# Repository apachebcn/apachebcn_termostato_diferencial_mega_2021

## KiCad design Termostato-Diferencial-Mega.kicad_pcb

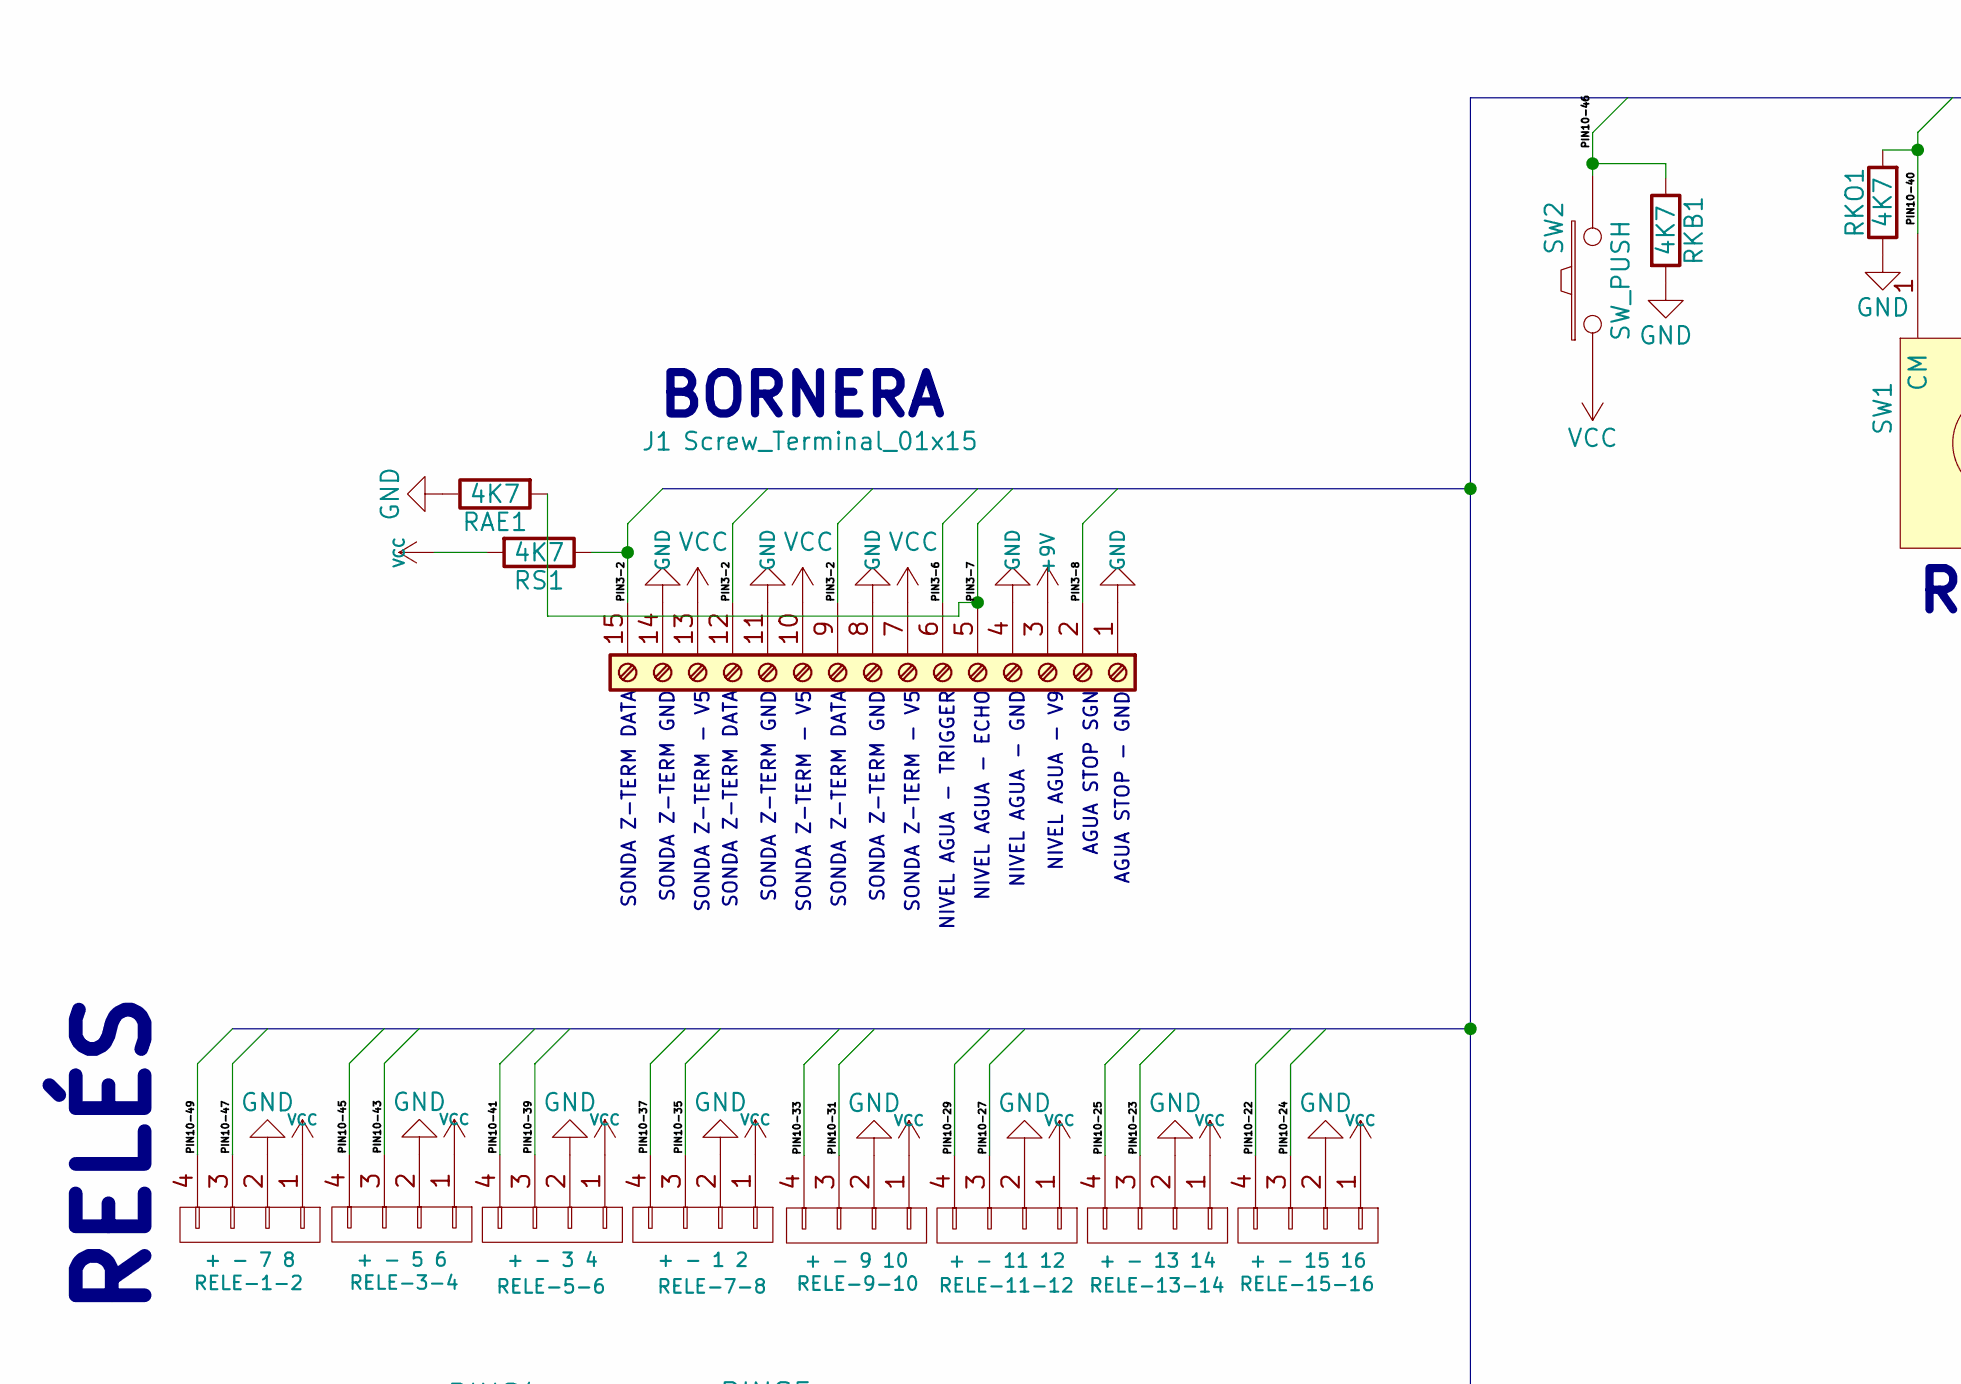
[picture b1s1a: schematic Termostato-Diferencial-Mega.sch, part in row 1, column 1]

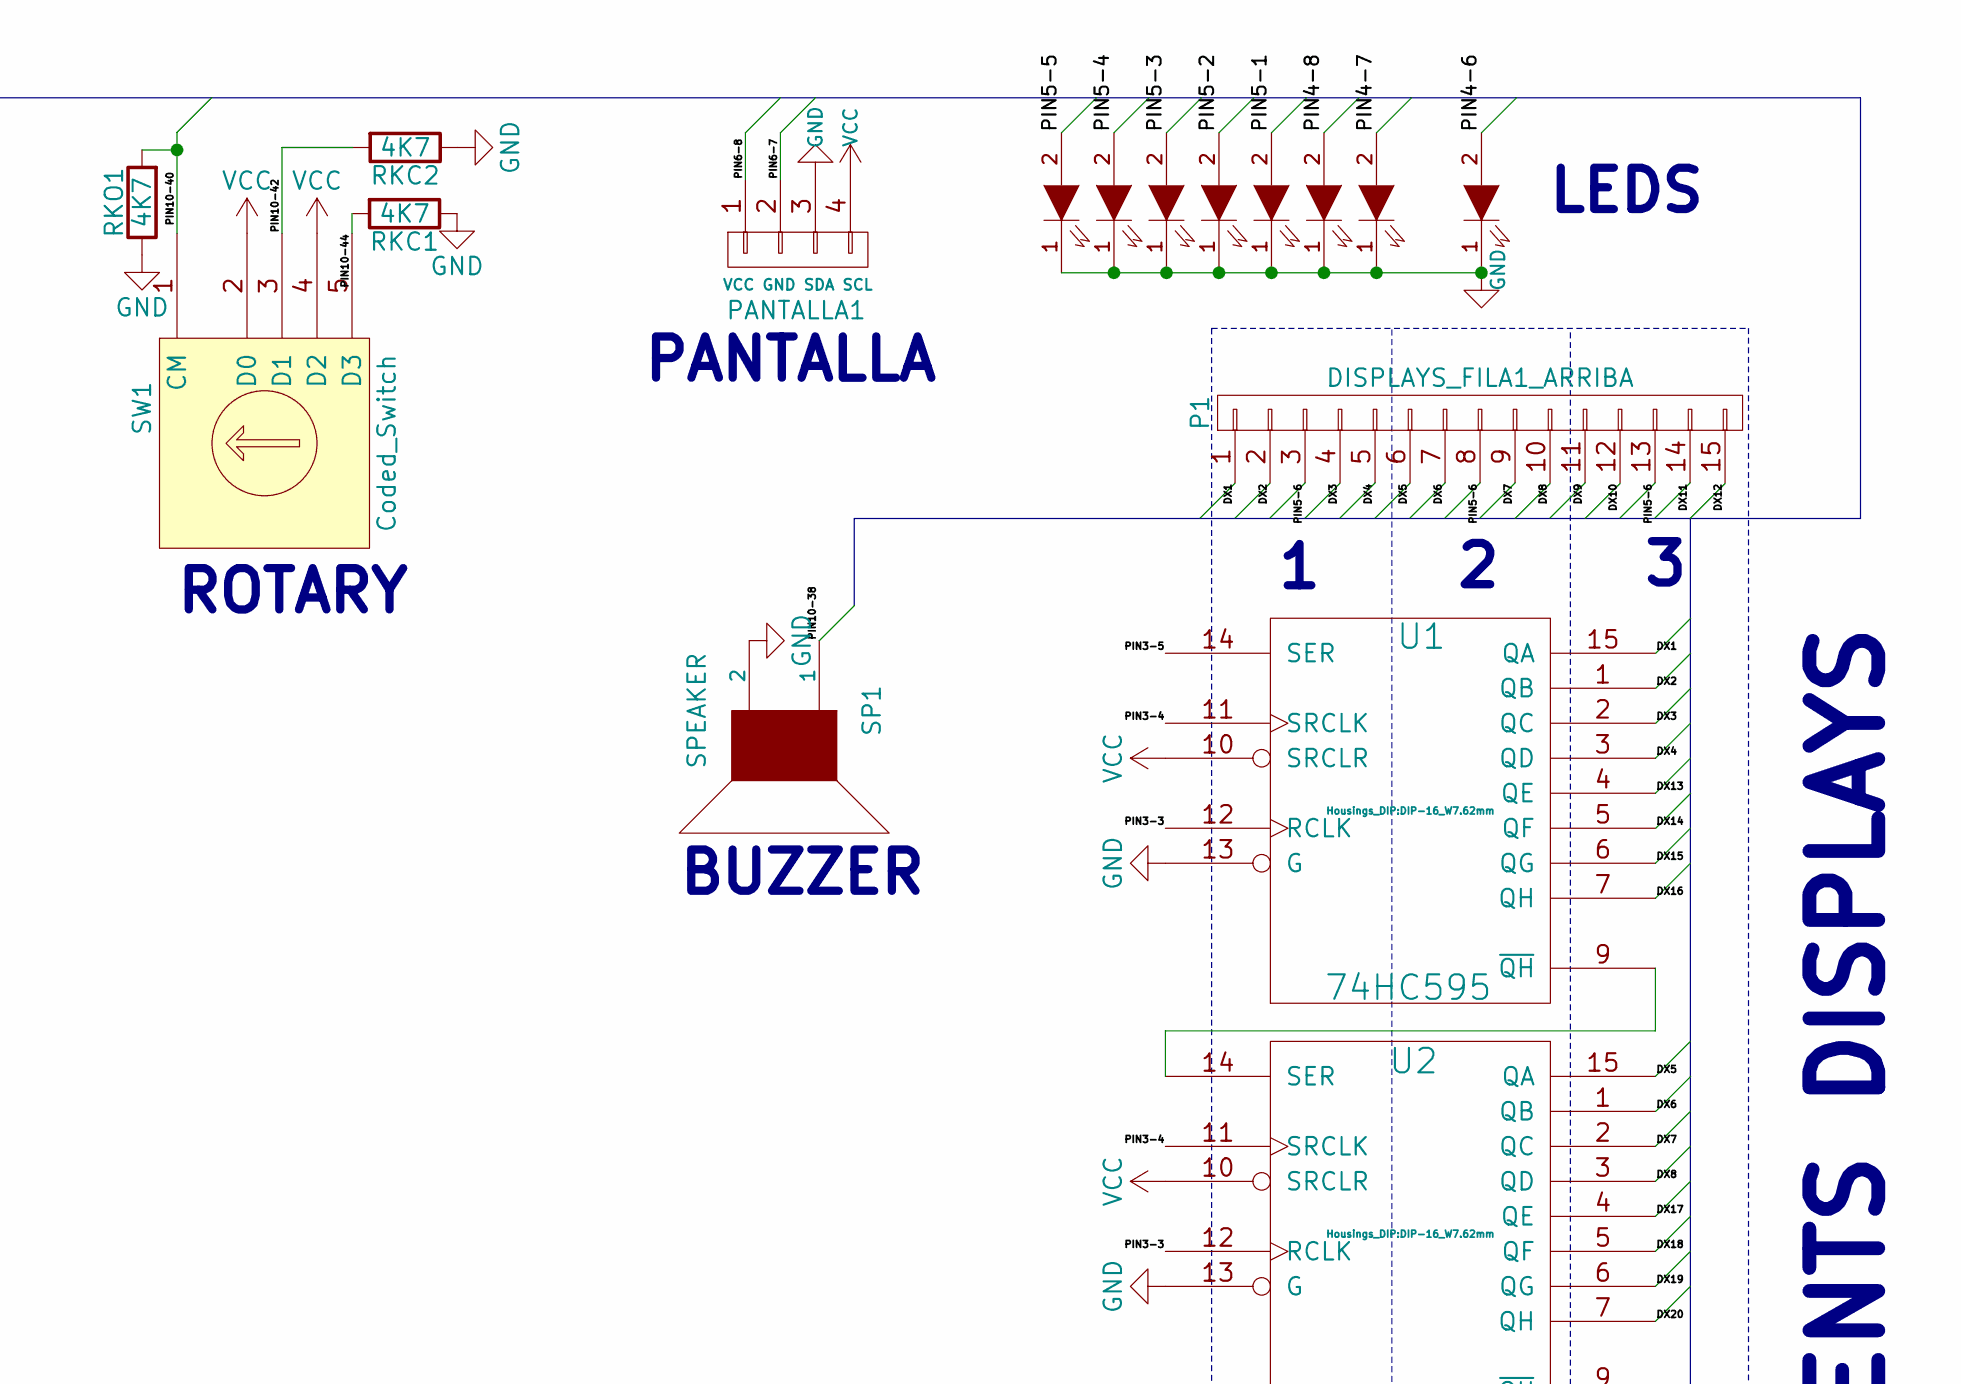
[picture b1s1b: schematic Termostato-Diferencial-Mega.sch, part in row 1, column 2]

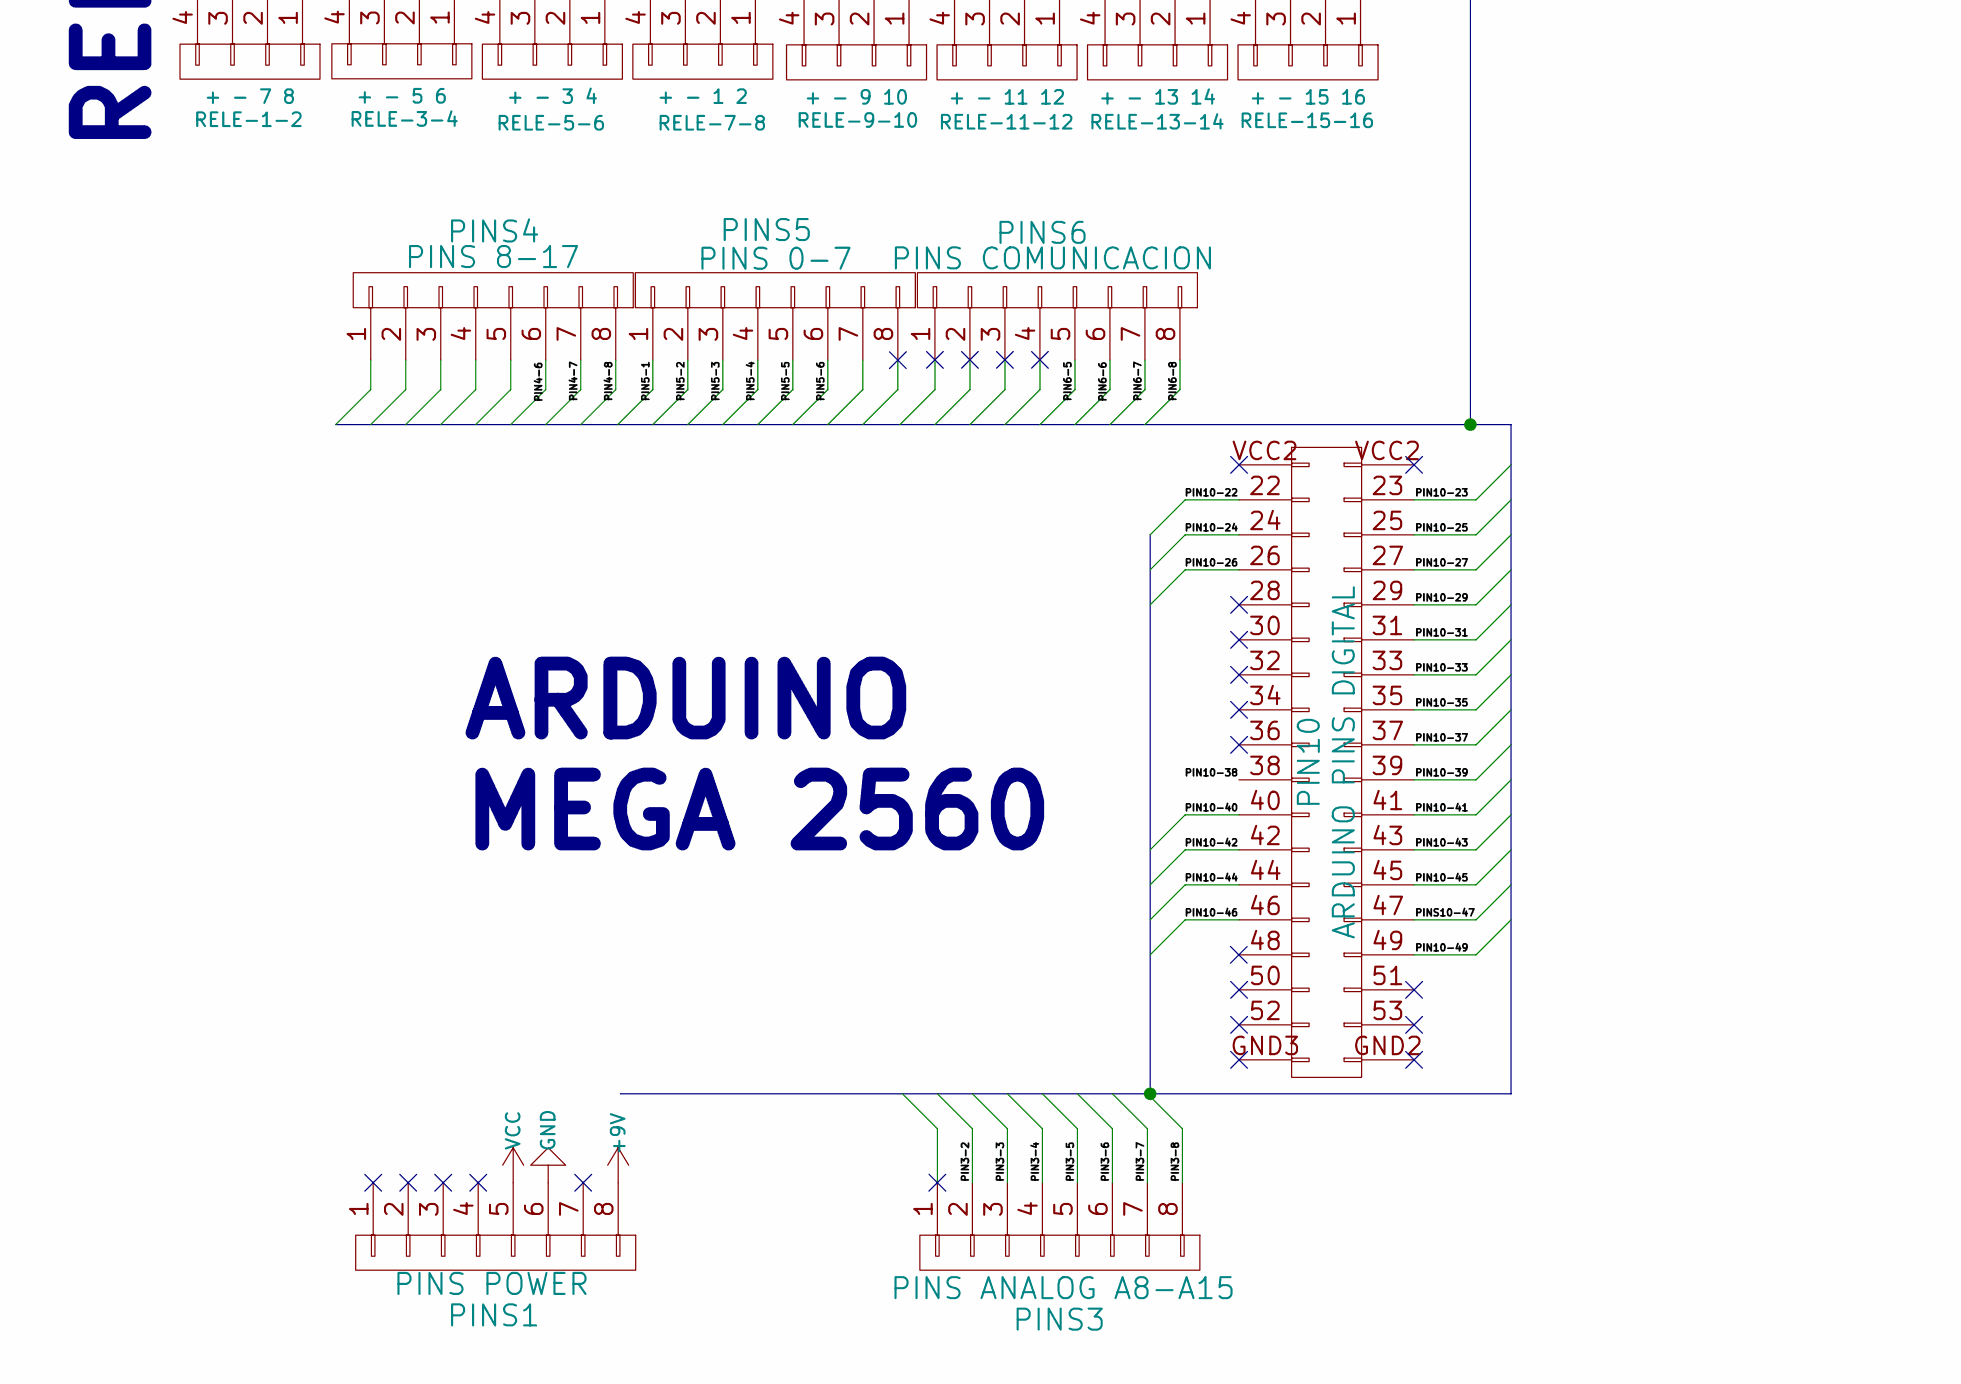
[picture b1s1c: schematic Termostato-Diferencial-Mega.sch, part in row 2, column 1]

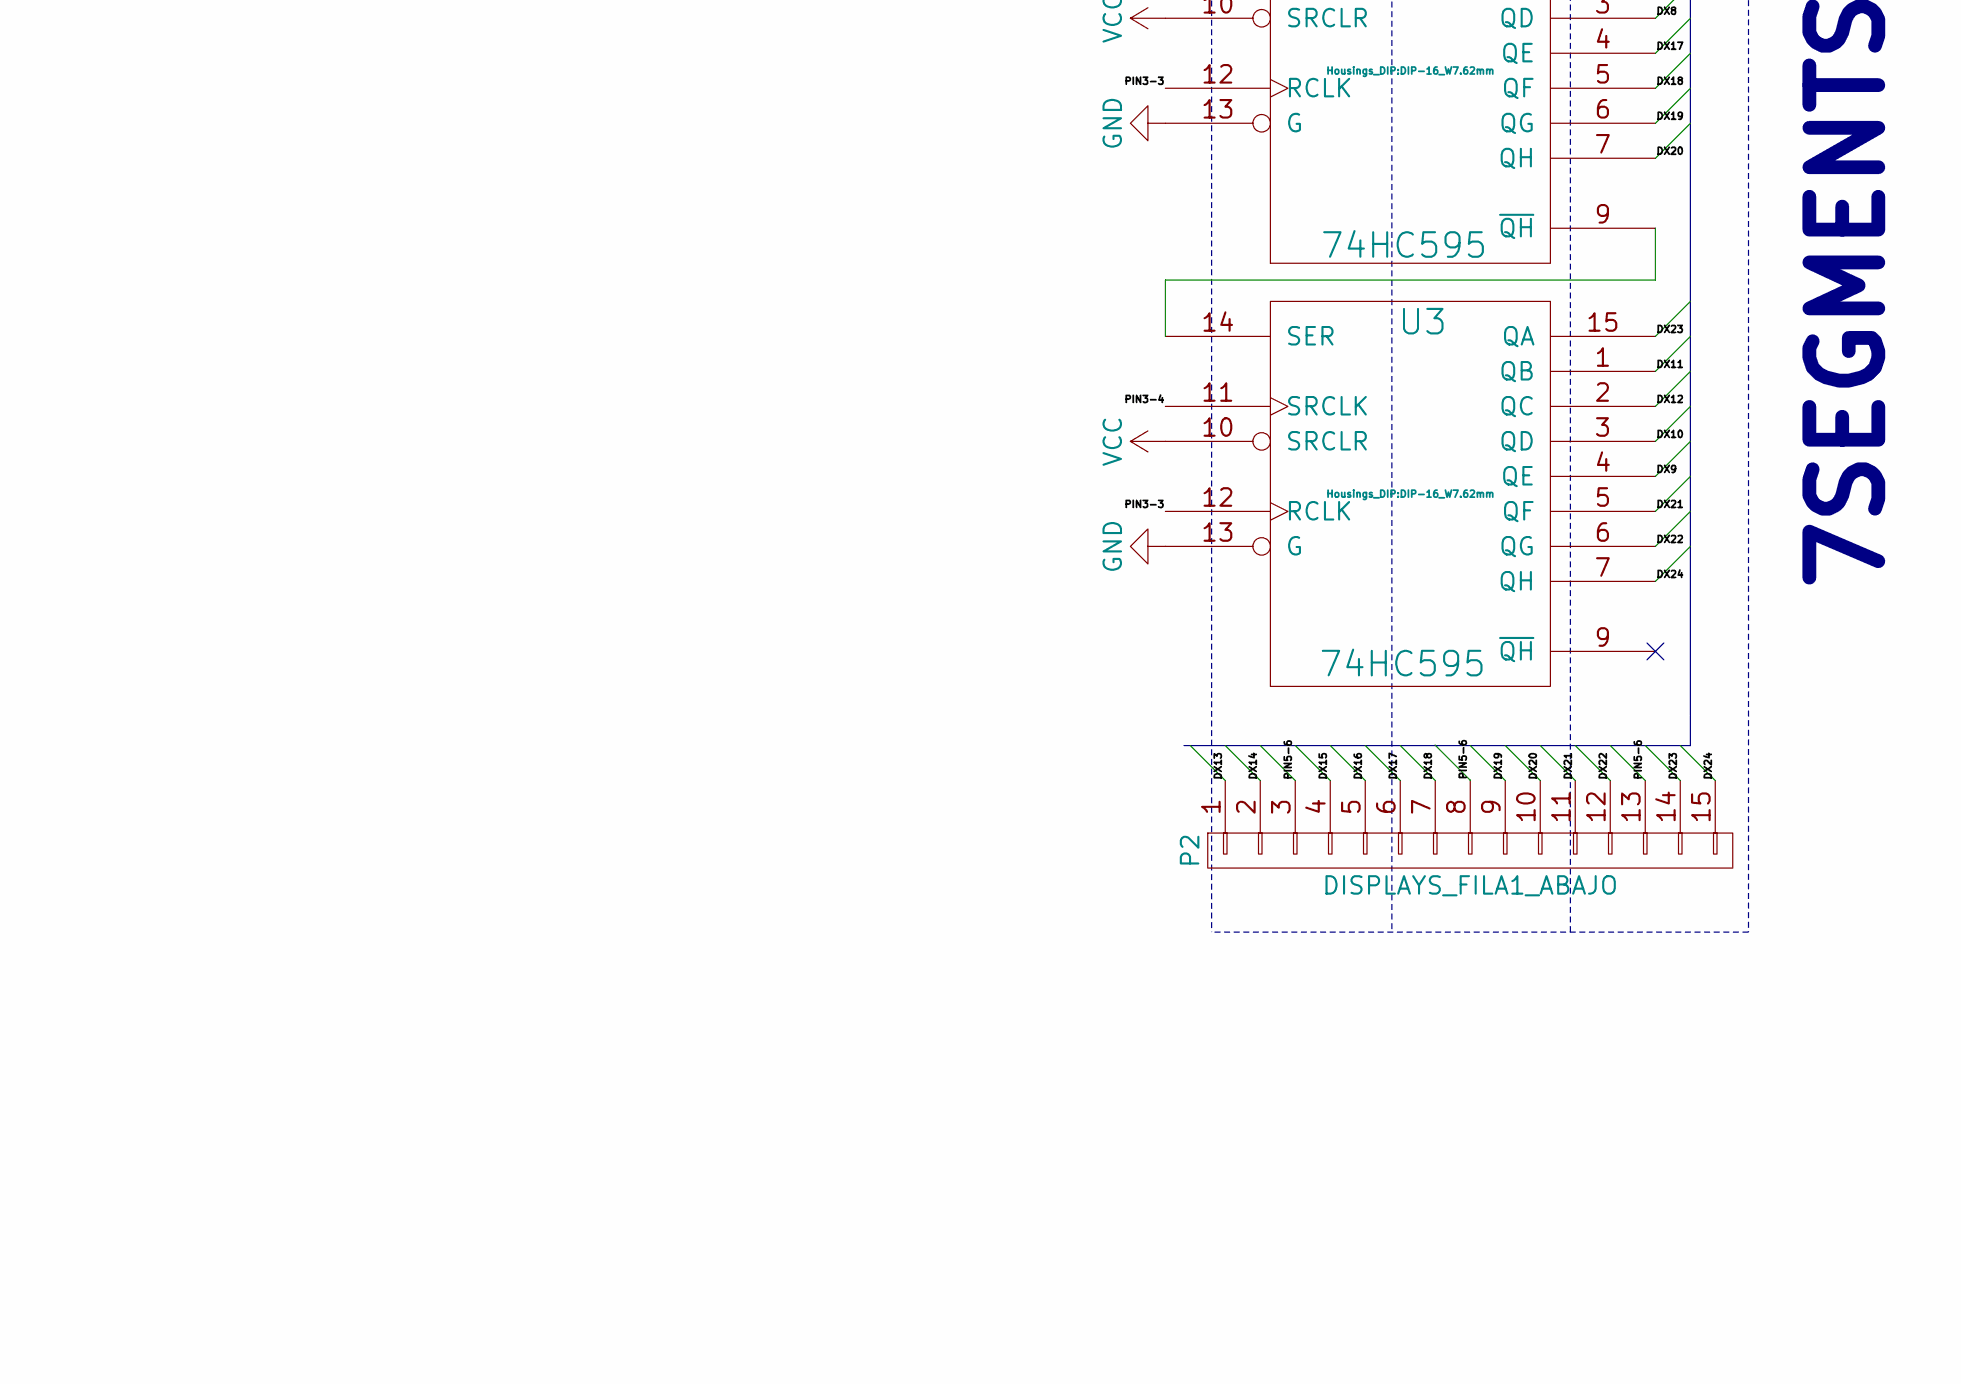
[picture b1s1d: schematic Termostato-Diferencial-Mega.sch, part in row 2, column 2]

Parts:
D1, D2, D3, D4, D5, D6, D7, D8: LED; LED_1206_3216Metric
J1: Screw_Terminal_01x15; TerminalBlock_Phoenix_MKDS-3-15-5.08_1x15_P5.08mm_Horizontal
P1: DISPLAYS_FILA1_ARRIBA; Socket_Strip_Straight_1x15
P2: DISPLAYS_FILA1_ABAJO; Socket_Strip_Straight_1x15
PANTALLA1: VCC GND SDA SCL; PinHeader_1x04_P2.54mm_Vertical
PIN10: ARDUINO PINS DIGITAL; PinHeader_2x18_P2.54mm_Vertical
PINS1: PINS POWER; PinHeader_1x08_P2.54mm_Vertical
PINS3: PINS ANALOG A8-A15; PinHeader_1x08_P2.54mm_Vertical
PINS4: PINS 8-17; PinHeader_1x08_P2.54mm_Vertical
PINS5: PINS 0-7; PinHeader_1x08_P2.54mm_Vertical
PINS6: PINS COMUNICACION; PinHeader_1x08_P2.54mm_Vertical
RAE1: 4K7; R_1206_3216Metric
RELE-1-2: + - 7 8; PinHeader_1x04_P2.54mm_Vertical
RELE-3-4: + - 5 6; PinHeader_1x04_P2.54mm_Vertical
RELE-5-6: + - 3 4; PinHeader_1x04_P2.54mm_Vertical
RELE-7-8: + - 1 2; PinHeader_1x04_P2.54mm_Vertical
RELE-9-10: + - 9 10; PinHeader_1x04_P2.54mm_Vertical
RELE-11-12: + - 11 12; PinHeader_1x04_P2.54mm_Vertical
RELE-13-14: + - 13 14; PinHeader_1x04_P2.54mm_Vertical
RELE-15-16: + - 15 16; PinHeader_1x04_P2.54mm_Vertical
RKB1: 4K7; R_1206_3216Metric
RKC1, RKC2: 4K7; R_1206_3216Metric
RKO1: 4K7; R_1206_3216Metric
RS1: 4K7; R_1206_3216Metric
SP1: SPEAKER; Buzzer_12x9.5RM7.6
SW1: Coded_Switch; KSA_Tactile_SPST
SW2: SW_PUSH; SW_PUSH-12mm
U1, U2, U3: 74HC595; DIP-16_W7.62mm

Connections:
+9V: J1.3, PINS1.8
/DX1: P1.1, U1.15 (QA)
/DX2: P1.2, U1.1 (QB)
/DX3: P1.4, U1.2 (QC)
/DX4: P1.5, U1.3 (QD)
/DX5: P1.6, U2.15 (QA)
/DX6: P1.7, U2.1 (QB)
/DX7: P1.9, U2.2 (QC)
/DX8: P1.10, U2.3 (QD)
/DX9: P1.11, U3.4 (QE)
/DX10: P1.12, U3.3 (QD)
/DX11: P1.14, U3.1 (QB)
/DX12: P1.15, U3.2 (QC)
/DX13: P2.1, U1.4 (QE)
/DX14: P2.2, U1.5 (QF)
/DX15: P2.4, U1.6 (QG)
/DX16: P2.5, U1.7 (QH)
/DX17: P2.6, U2.4 (QE)
/DX18: P2.7, U2.5 (QF)
/DX19: P2.9, U2.6 (QG)
/DX20: P2.10, U2.7 (QH)
/DX21: P2.11, U3.5 (QF)
/DX22: P2.12, U3.6 (QG)
/DX23: P2.14, U3.15 (QA)
/DX24: P2.15, U3.7 (QH)
/PIN3-2: J1.9, J1.12, J1.15, PINS3.2, RS1.1
/PIN3-3: PINS3.3, U1.12 (RCLK), U2.12 (RCLK), U3.12 (RCLK)
/PIN3-4: PINS3.4, U1.11 (SRCLK), U2.11 (SRCLK), U3.11 (SRCLK)
/PIN3-5: PINS3.5, U1.14 (SER)
/PIN3-6: J1.6, PINS3.6
/PIN3-7: J1.5, PINS3.7, RAE1.2
/PIN3-8: J1.2, PINS3.8
/PIN4-6: D1.2 (A), PINS4.6
/PIN4-7: D2.2 (A), PINS4.7
/PIN4-8: D3.2 (A), PINS4.8
/PIN5-1: D4.2 (A), PINS5.1
/PIN5-2: D5.2 (A), PINS5.2
/PIN5-3: D6.2 (A), PINS5.3
/PIN5-4: D7.2 (A), PINS5.4
/PIN5-5: D8.2 (A), PINS5.5
/PIN5-6: P1.3, P1.8, P1.13, P2.3, P2.8, P2.13, PINS5.6
/PIN6-7: PANTALLA1.2, PINS6.7
/PIN6-8: PANTALLA1.1, PINS6.8
/PIN10-22: PIN10.22, RELE-15-16.4
/PIN10-23: PIN10.23, RELE-13-14.3
/PIN10-24: PIN10.24, RELE-15-16.3
/PIN10-25: PIN10.25, RELE-13-14.4
/PIN10-26: PIN10.26
/PIN10-27: PIN10.27, RELE-11-12.3
/PIN10-29: PIN10.29, RELE-11-12.4
/PIN10-31: PIN10.31, RELE-9-10.3
/PIN10-33: PIN10.33, RELE-9-10.4
/PIN10-35: PIN10.35, RELE-7-8.3
/PIN10-37: PIN10.37, RELE-7-8.4
/PIN10-38: PIN10.38, SP1.1
/PIN10-39: PIN10.39, RELE-5-6.3
/PIN10-40: PIN10.40, RKO1.2, SW1.1 (CM)
/PIN10-41: PIN10.41, RELE-5-6.4
/PIN10-42: PIN10.42, RKC2.2, SW1.3 (D1)
/PIN10-43: PIN10.43, RELE-3-4.3
/PIN10-44: PIN10.44, RKC1.2, SW1.5 (D3)
/PIN10-45: PIN10.45, RELE-3-4.4
/PIN10-46: PIN10.46, RKB1.1, SW2.2
/PIN10-49: PIN10.49, RELE-1-2.4
GND: D1.1 (K), D2.1 (K), D3.1 (K), D4.1 (K), D5.1 (K), D6.1 (K), D7.1 (K), D8.1 (K), J1.1, J1.4, J1.8, J1.11, J1.14, PANTALLA1.3, PINS1.6, RAE1.1, RELE-1-2.2, RELE-3-4.2, RELE-5-6.2, RELE-7-8.2, RELE-9-10.2, RELE-11-12.2, RELE-13-14.2, RELE-15-16.2, RKB1.2, RKC1.1, RKC2.1, RKO1.1, SP1.2, U1.8 (GND), U1.13 (G), U2.8 (GND), U2.13 (G), U3.8 (GND), U3.13 (G)
unnamed: U1.9 (~QH), U2.14 (SER)
unnamed: U2.9 (~QH), U3.14 (SER)
VCC: J1.7, J1.10, J1.13, PANTALLA1.4, PINS1.5, RELE-1-2.1, RELE-3-4.1, RELE-5-6.1, RELE-7-8.1, RELE-9-10.1, RELE-11-12.1, RELE-13-14.1, RELE-15-16.1, RS1.2, SW1.2 (D0), SW1.4 (D2), SW2.1, U1.10 (SRCLR), U1.16 (VCC), U2.10 (SRCLR), U2.16 (VCC), U3.10 (SRCLR), U3.16 (VCC)

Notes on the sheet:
AGUA STOP SGN
NIVEL AGUA - V9
NIVEL AGUA - GND
AGUA STOP - GND
NIVEL AGUA - ECHO
SONDA Z-TERM - V5
SONDA Z-TERM GND
SONDA Z-TERM DATA
NIVEL AGUA - TRIGGER
ARDUINO MEGA 2560
RELÉS
7SEGMENTS DISPLAYS
PANTALLA
LEDS
ROTARY
BORNERA
BUZZER

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
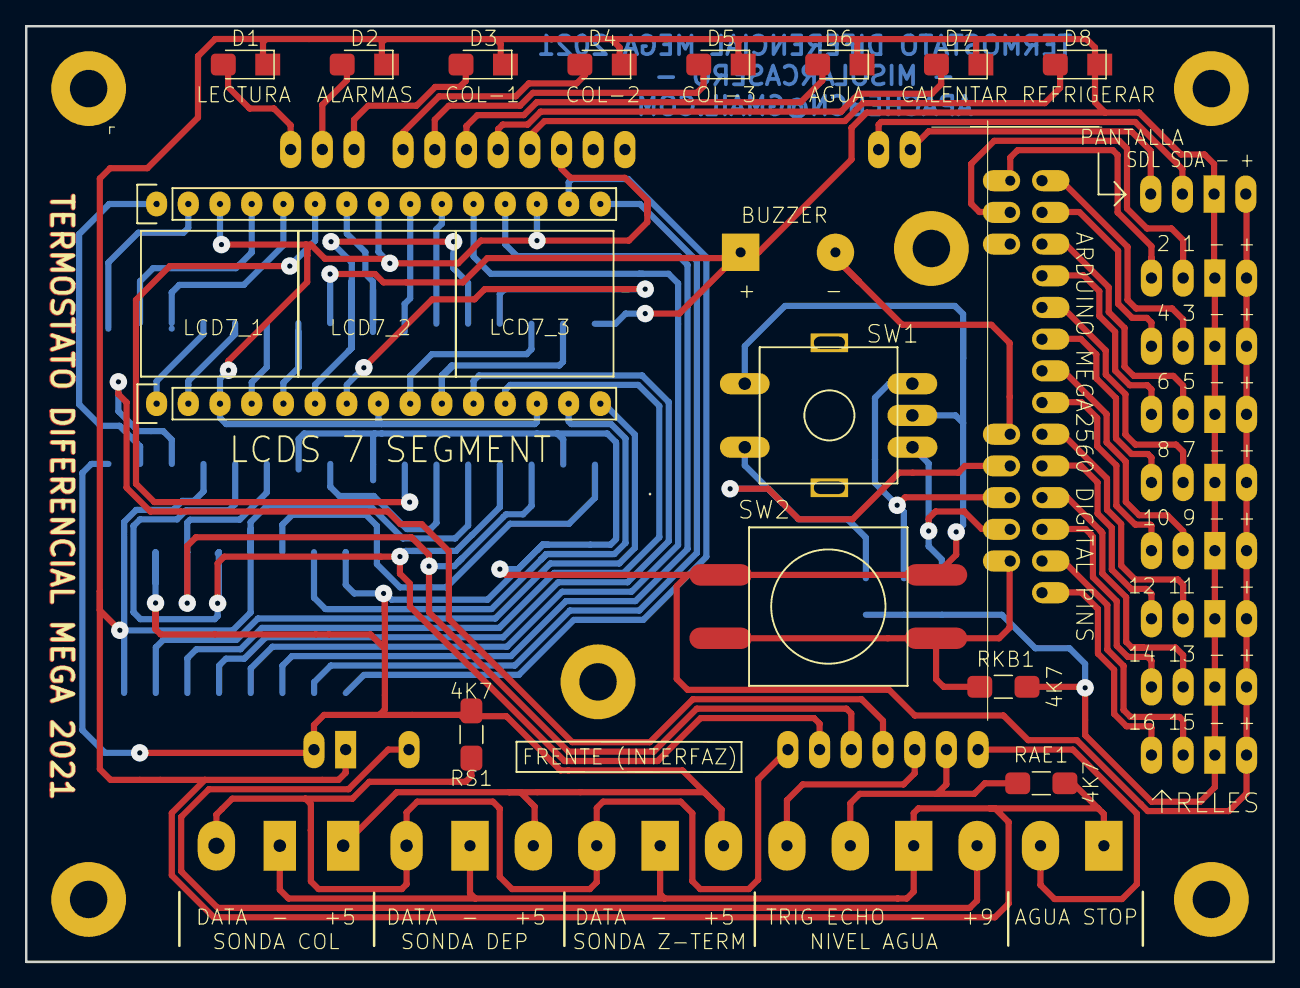
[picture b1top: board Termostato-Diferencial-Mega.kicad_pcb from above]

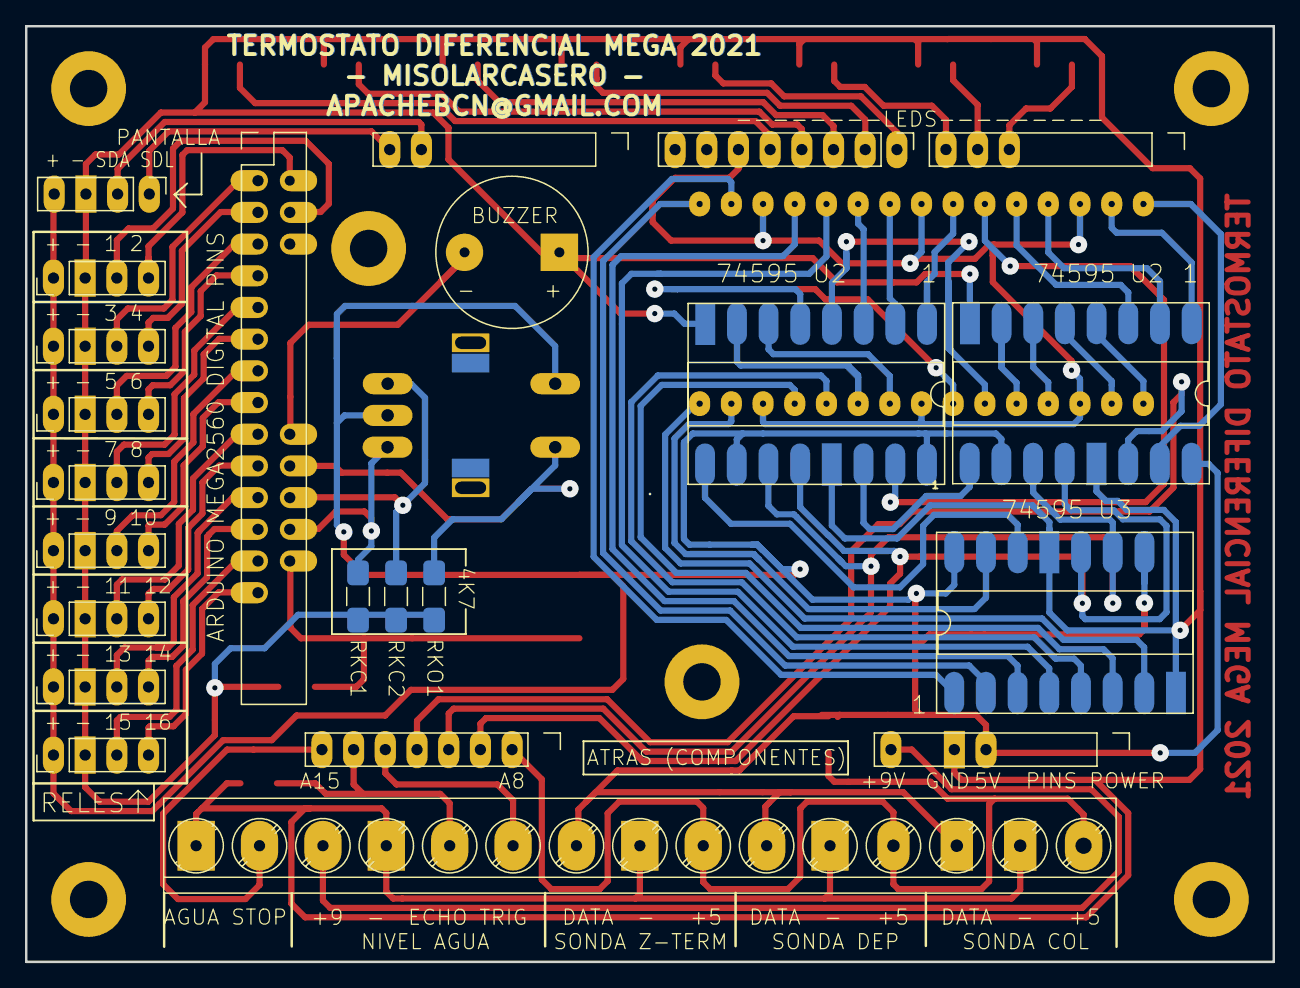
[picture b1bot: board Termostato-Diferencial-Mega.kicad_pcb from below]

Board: 2 copper layers, 100.0 x 75.0 mm, 44 parts (23 on the bottom side), 68 nets.

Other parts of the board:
TORNILLO-1, TORNILLO-2, TORNILLO-3, TORNILLO-4, TORNILLO-5, TORNILLO-6: MountingHole_3mm_Pad

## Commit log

2024-09-16 color del pcb en 3d
2024-09-16 remove GCODE folder
